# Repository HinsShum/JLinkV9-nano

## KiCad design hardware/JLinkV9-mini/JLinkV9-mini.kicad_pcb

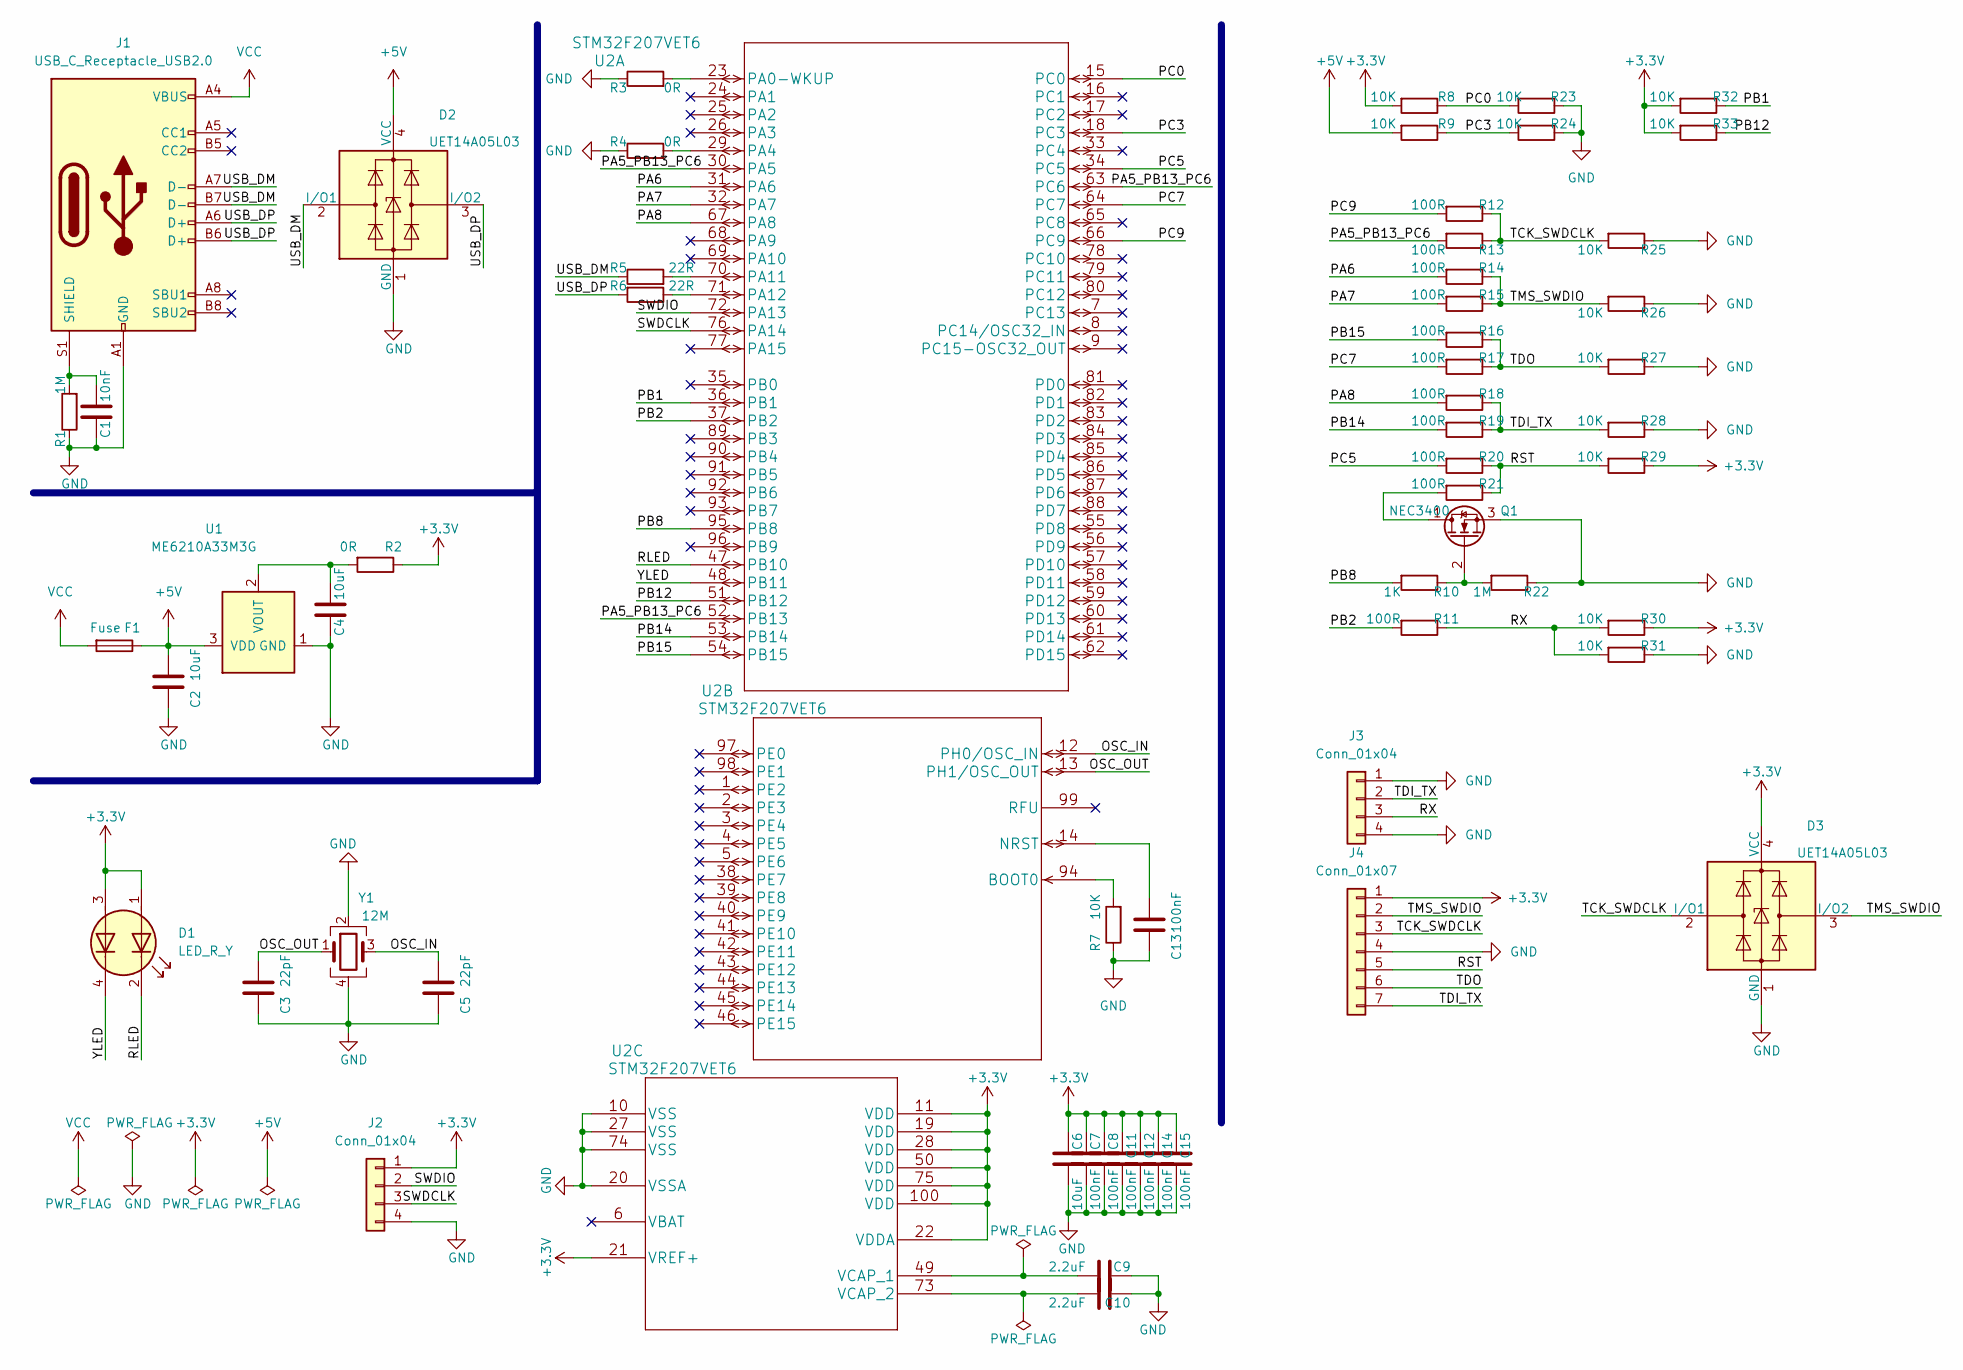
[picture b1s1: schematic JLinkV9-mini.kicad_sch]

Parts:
C1: 10nF; C_0402_1005Metric
C2, C4, C6: 10uF; C_0603_1608Metric
C3, C5: 22pF; C_0402_1005Metric
C7, C8, C11, C12, C13, C14, C15: 100nF; C_0402_1005Metric
C9, C10: 2.2uF; C_0402_1005Metric
D1: LED_R_Y; LED_Dual_0606
D2, D3: UET14A05L03; SOT-143
F1: Fuse; Fuse_0603_1608Metric
J1: USB_C_Receptacle_USB2.0; USB_C_Receptacle_HRO_TYPE-C-31-M-12
J2, J3: Conn_01x04; PinHeader_1x04_P2.00mm_Vertical
J4: Conn_01x07; PinHeader_1x07_P2.00mm_Vertical
Q1: NEC3400; SOT-23
R1, R22: 1M; R_0402_1005Metric
R2: 0R; R_0603_1608Metric
R3, R4: 0R; R_0402_1005Metric
R5, R6: 22R; R_0402_1005Metric
R7, R8, R9, R23, R24, R25, R26, R27, R28, R29, R30, R31, R32, R33: 10K; R_0402_1005Metric
R10: 1K; R_0402_1005Metric
R11, R12, R13, R14, R15, R16, R17, R18, R19, R20, R21: 100R; R_0402_1005Metric
U1: ME6210A33M3G; SOT-23
U2: STM32F207VET6; LQFP-100_14x14mm_P0.5mm
Y1: 12M; Crystal_SMD_3225-4Pin_3.2x2.5mm

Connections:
+3.3V: C6.2, C7.2, C8.2, C11.2, C12.2, C14.2, C15.2, D1.1 (A1), D1.3 (A2), D3.4 (VCC), J2.1, J4.1, R2.1, R8.2, R29.1, R30.1, R32.2, R33.2, U2.11 (VDD), U2.19 (VDD), U2.21 (VREF+), U2.22 (VDDA), U2.28 (VDD), U2.50 (VDD), U2.75 (VDD), U2.100 (VDD)
+5V: C2.1, D2.4 (VCC), F1.1, R9.2, U1.3 (VDD)
/OSC_IN: C5.1, U2.12 (PH0/OSC_IN), Y1.3
/OSC_OUT: C3.1, U2.13 (PH1/OSC_OUT), Y1.1
/PA5_PB13_PC6: R13.2, U2.30 (PA5), U2.52 (PB13), U2.63 (PC6)
/PA6: R14.2, U2.31 (PA6)
/PA7: R15.2, U2.32 (PA7)
/PA8: R18.2, U2.67 (PA8)
/PB1: R32.1, U2.36 (PB1)
/PB2: R11.2, U2.37 (PB2)
/PB8: R10.2, U2.95 (PB8)
/PB12: R33.1, U2.51 (PB12)
/PB14: R19.2, U2.53 (PB14)
/PB15: R16.2, U2.54 (PB15)
/PC0: R8.1, R23.2, U2.15 (PC0)
/PC3: R9.1, R24.2, U2.18 (PC3)
/PC5: R20.2, U2.34 (PC5)
/PC7: R17.2, U2.64 (PC7)
/PC9: R12.2, U2.66 (PC9)
/RLED: D1.2 (K1), U2.47 (PB10)
/RST: J4.5, R20.1, R21.1, R29.2
/RX: J3.3, R11.1, R30.2, R31.2
/SWDCLK: J2.3, U2.76 (PA14)
/SWDIO: J2.2, U2.72 (PA13)
/TCK_SWDCLK: D3.2 (I/O1), J4.3, R12.1, R13.1, R25.2
/TDI_TX: J3.2, J4.7, R18.1, R19.1, R28.2
/TDO: J4.6, R16.1, R17.1, R27.2
/TMS_SWDIO: D3.3 (I/O2), J4.2, R14.1, R15.1, R26.2
/USB_DM: D2.2 (I/O1), J1.A7 (D-), J1.B7 (D-), R5.1
/USB_DP: D2.3 (I/O2), J1.A6 (D+), J1.B6 (D+), R6.2
/YLED: D1.4 (K2), U2.48 (PB11)
GND: C1.2, C2.2, C3.2, C4.2, C5.2, C6.1, C7.1, C8.1, C9.2, C10.2, C11.1, C12.1, C13.2, C14.1, C15.1, D2.1 (GND), D3.1 (GND), J1.A1 (GND), J1.A12 (GND), J1.B1 (GND), J1.B12 (GND), J2.4, J3.1, J3.4, J4.4, Q1.3 (S), R1.1, R3.1, R4.1, R7.1, R22.1, R23.1, R24.1, R25.1, R26.1, R27.1, R28.1, R31.1, U1.1 (GND), U2.10 (VSS), U2.20 (VSSA), U2.27 (VSS), U2.74 (VSS), Y1.2, Y1.4
unnamed: C1.1, J1.S1 (SHIELD), R1.2
unnamed: C4.1, R2.2, U1.2 (VOUT)
unnamed: C9.1, U2.49 (VCAP_1)
unnamed: C10.1, U2.73 (VCAP_2)
unnamed: C13.1, U2.14 (NRST)
unnamed: Q1.1 (D), R21.2
unnamed: Q1.2 (G), R10.1, R22.2
unnamed: R3.2, U2.23 (PA0-WKUP)
unnamed: R4.2, U2.29 (PA4)
unnamed: R5.2, U2.70 (PA11)
unnamed: R6.1, U2.71 (PA12)
unnamed: R7.2, U2.94 (BOOT0)
VCC: F1.2, J1.A4 (VBUS), J1.A9 (VBUS), J1.B4 (VBUS), J1.B9 (VBUS)

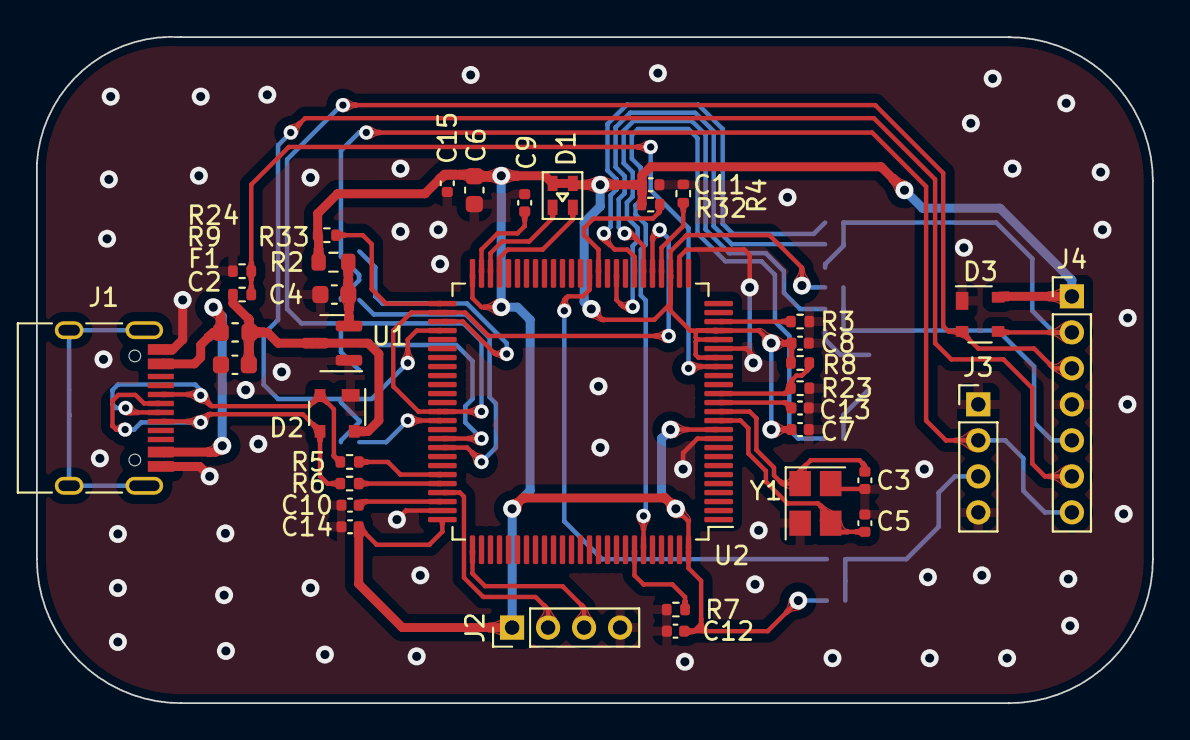
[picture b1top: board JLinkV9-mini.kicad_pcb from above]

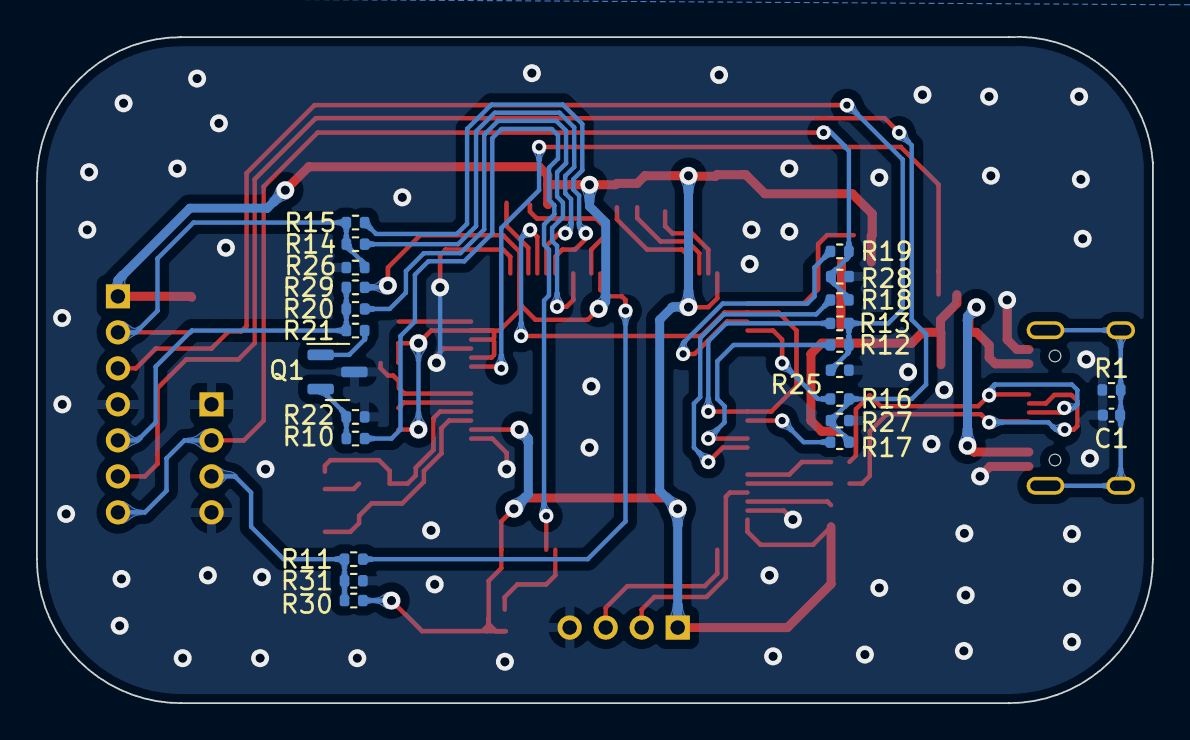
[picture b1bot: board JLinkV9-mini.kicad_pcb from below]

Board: 2 copper layers, 62.0 x 37.0 mm, 60 parts (23 on the bottom side), 45 nets.

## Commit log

2021-11-25 <Add>: Create item
2021-12-11 <Add>: complete sch for jlinkv9-nano
2021-12-27 <Add>: complete layout
2022-02-19 <Modify>: update layout
2022-11-06 feat: create kicad project for JLinkV9-mini
2022-11-06 feat: update gerbers for JLinkV9-mini
2022-11-06 feat: update JLinkV9-mini sch
2022-11-06 feat: update jlinkv9-mini pcb
